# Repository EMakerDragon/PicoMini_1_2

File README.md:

RP2040とRP2350Aの小型開発ボードです。  
かなり適当な設計なので参考程度にしてください。  
JLCPCBの4層で製造しています。

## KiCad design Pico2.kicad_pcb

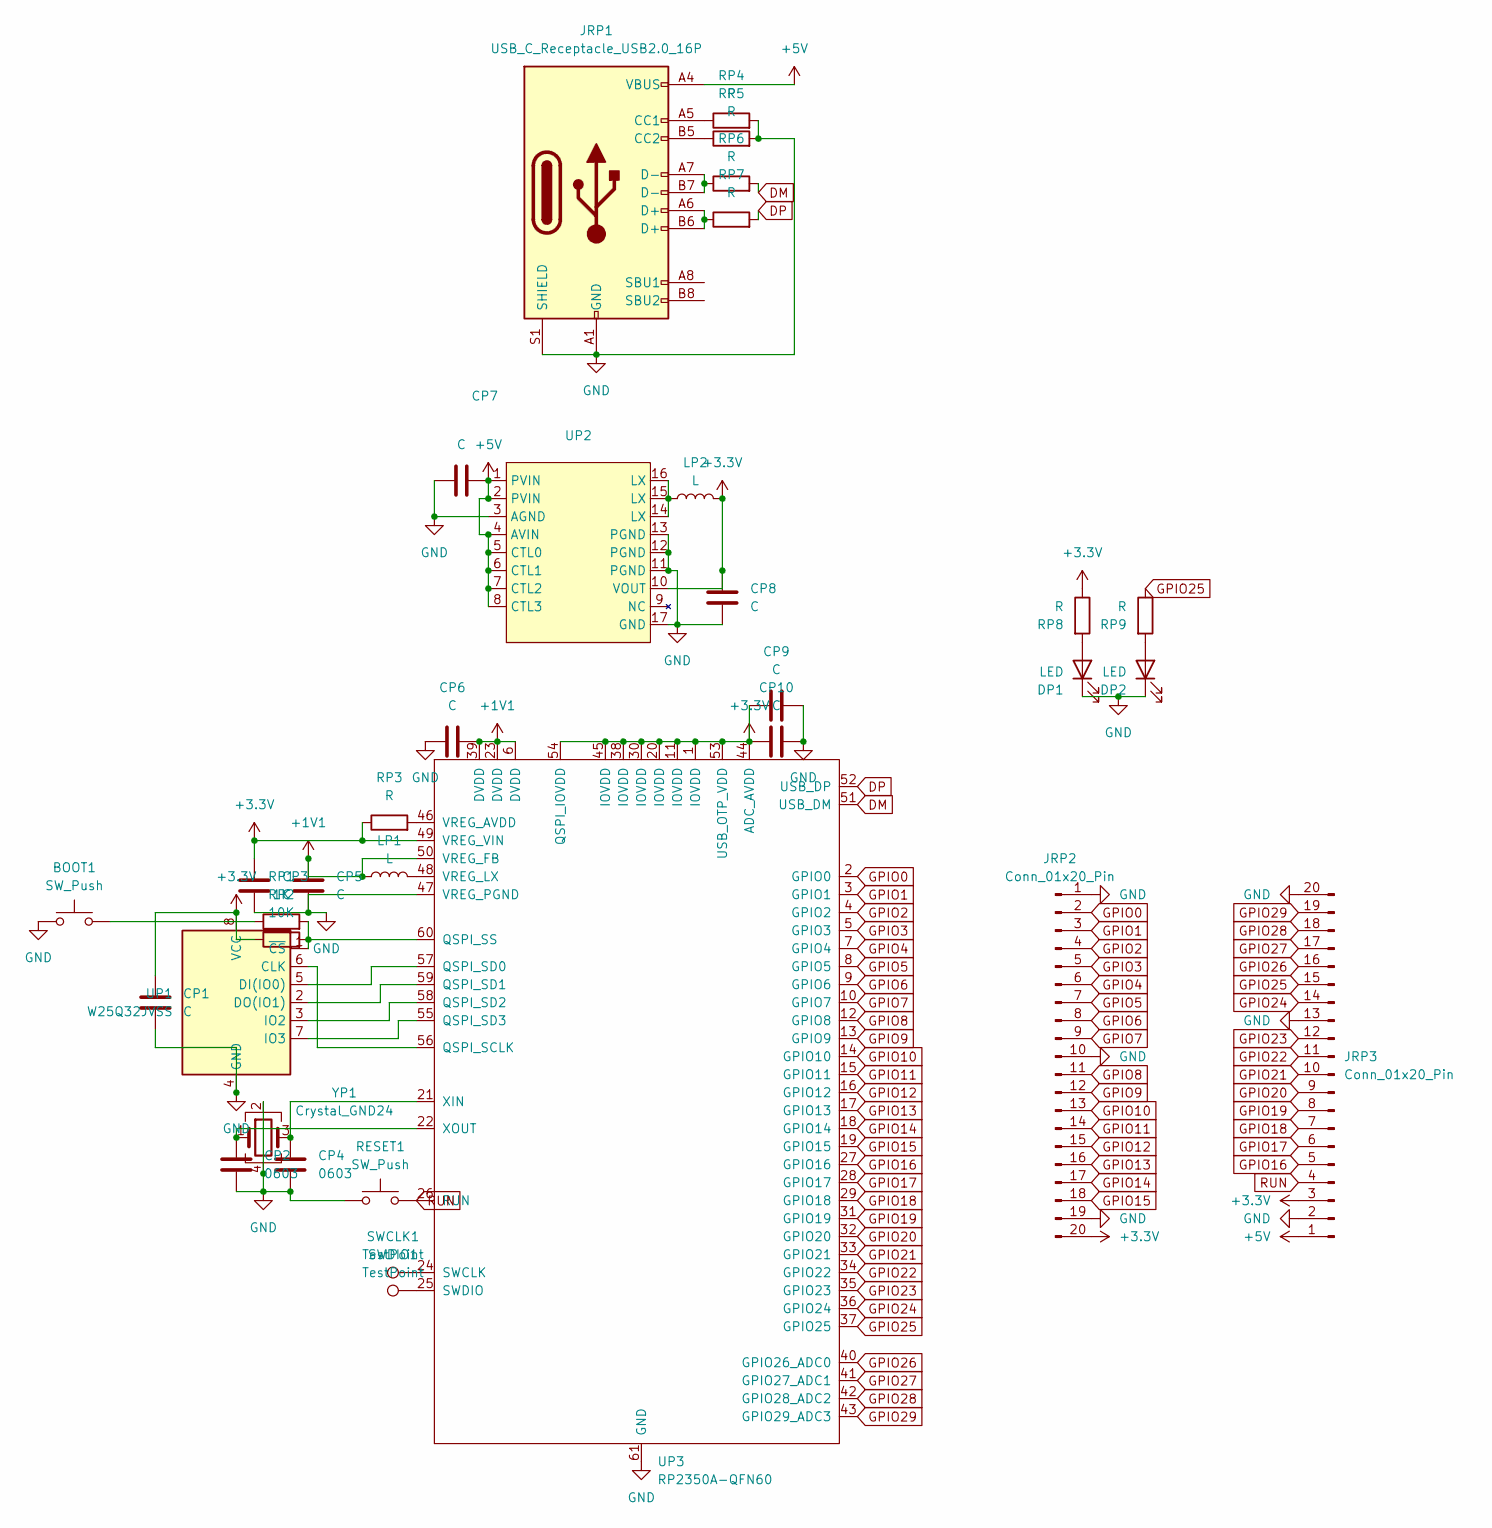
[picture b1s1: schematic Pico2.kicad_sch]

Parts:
BOOT1: SW_Push; SKRMAAE010
CP1, CP3, CP5, CP6, CP7, CP8, CP9, CP10: C; C_0805_2012Metric
CP2, CP4: 0603; C_0603_1608Metric
DP1, DP2: LED; LED_0805_2012Metric
JRP1: USB_C_Receptacle_USB2.0_16P; USB_C_Receptacle_G-Switch_GT-USB-7010ASV
JRP2, JRP3: Conn_01x20_Pin; PinHeader_1x20_P2.54mm_Vertical
LP1, LP2: L; L_1008_2520Metric
RESET1: SW_Push; SKRMAAE010
RP1: 1K; R_0603_1608Metric
RP2: 10K; R_0603_1608Metric
RP3, RP4, RP5, RP6, RP7, RP8, RP9: R; R_0603_1608Metric
SWCLK1: TestPoint; TestPoint_Pad_D1.0mm
SWDIO1: TestPoint; TestPoint_Pad_D1.0mm
UP1: W25Q32JVSS; U-PDFN-8
UP2: QFN-16-1EP_3x3mm_P0.5mm_EP1.7x1.7mm
UP3: RP2350A-QFN60; RP2350A_QFN-60_EP_7.75x7.75_Pitch0.4mm
YP1: Crystal_GND24; Crystal_SMD_SeikoEpson_TSX3225-4Pin_3.2x2.5mm

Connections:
+1V1: CP5.2, CP6.2, LP1.1, UP3.6 (DVDD), UP3.23 (DVDD), UP3.39 (DVDD), UP3.50 (VREG_FB)
+3.3V: CP1.2, CP3.2, CP8.1, CP9.1, CP10.1, JRP2.20, JRP3.3, LP2.2, RP2.1, RP3.1, RP8.1, UP1.8 (VCC), UP2.10 (VOUT), UP3.1 (IOVDD), UP3.11 (IOVDD), UP3.20 (IOVDD), UP3.30 (IOVDD), UP3.38 (IOVDD), UP3.44 (ADC_AVDD), UP3.45 (IOVDD), UP3.49 (VREG_VIN), UP3.53 (USB_OTP_VDD), UP3.54 (QSPI_IOVDD)
+5V: CP7.2, JRP1.A4 (VBUS), JRP1.A9 (VBUS), JRP1.B4 (VBUS), JRP1.B9 (VBUS), JRP3.1, UP2.1 (PVIN), UP2.2 (PVIN), UP2.4 (AVIN), UP2.5 (CTL0), UP2.6 (CTL1), UP2.7 (CTL2), UP2.8 (CTL3)
DM: RP6.2, UP3.51 (USB_DM)
DP: RP7.2, UP3.52 (USB_DP)
GND: BOOT1.1, CP1.1, CP2.2, CP3.1, CP4.2, CP5.1, CP6.1, CP7.1, CP8.2, CP9.2, CP10.2, DP1.1 (K), DP2.1 (K), JRP1.A1 (GND), JRP1.A12 (GND), JRP1.B1 (GND), JRP1.B12 (GND), JRP1.S1 (SHIELD), JRP2.1, JRP2.10, JRP2.19, JRP3.2, JRP3.13, JRP3.20, RESET1.1, RP4.2, RP5.2, UP1.4 (GND), UP2.3 (AGND), UP2.11 (PGND), UP2.12 (PGND), UP2.13 (PGND), UP2.17 (GND), UP3.47 (VREG_PGND), UP3.61 (GND), YP1.2, YP1.4
GPIO0: JRP2.2, UP3.2 (GPIO0)
GPIO1: JRP2.3, UP3.3 (GPIO1)
GPIO2: JRP2.4, UP3.4 (GPIO2)
GPIO3: JRP2.5, UP3.5 (GPIO3)
GPIO4: JRP2.6, UP3.7 (GPIO4)
GPIO5: JRP2.7, UP3.8 (GPIO5)
GPIO6: JRP2.8, UP3.9 (GPIO6)
GPIO7: JRP2.9, UP3.10 (GPIO7)
GPIO8: JRP2.11, UP3.12 (GPIO8)
GPIO9: JRP2.12, UP3.13 (GPIO9)
GPIO10: JRP2.13, UP3.14 (GPIO10)
GPIO11: JRP2.14, UP3.15 (GPIO11)
GPIO12: JRP2.15, UP3.16 (GPIO12)
GPIO13: JRP2.16, UP3.17 (GPIO13)
GPIO14: JRP2.17, UP3.18 (GPIO14)
GPIO15: JRP2.18, UP3.19 (GPIO15)
GPIO16: JRP3.5, UP3.27 (GPIO16)
GPIO17: JRP3.6, UP3.28 (GPIO17)
GPIO18: JRP3.7, UP3.29 (GPIO18)
GPIO19: JRP3.8, UP3.31 (GPIO19)
GPIO20: JRP3.9, UP3.32 (GPIO20)
GPIO21: JRP3.10, UP3.33 (GPIO21)
GPIO22: JRP3.11, UP3.34 (GPIO22)
GPIO23: JRP3.12, UP3.35 (GPIO23)
GPIO24: JRP3.14, UP3.36 (GPIO24)
GPIO25: JRP3.15, RP9.1, UP3.37 (GPIO25)
GPIO26: JRP3.16, UP3.40 (GPIO26_ADC0)
GPIO27: JRP3.17, UP3.41 (GPIO27_ADC1)
GPIO28: JRP3.18, UP3.42 (GPIO28_ADC2)
GPIO29: JRP3.19, UP3.43 (GPIO29_ADC3)
unnamed: BOOT1.2, RP1.1
unnamed: DP1.2 (A), RP8.2
unnamed: DP2.2 (A), RP9.2
unnamed: JRP1.A5 (CC1), RP4.1
unnamed: JRP1.B5 (CC2), RP5.1
unnamed: JRP1.A6 (D+), JRP1.B6 (D+), RP7.1
unnamed: JRP1.A7 (D-), JRP1.B7 (D-), RP6.1
unnamed: LP2.1, UP2.14 (LX), UP2.15 (LX), UP2.16 (LX)
unnamed: UP1.6 (CLK), UP3.56 (QSPI_SCLK)
unnamed: UP1.5 (DI(IO0)), UP3.57 (QSPI_SD0)
unnamed: UP1.2 (DO(IO1)), UP3.59 (QSPI_SD1)
unnamed: UP1.3 (IO2), UP3.58 (QSPI_SD2)
unnamed: UP1.7 (IO3), UP3.55 (QSPI_SD3)
unnamed: RP1.2, RP2.2, UP1.1 (~CS), UP3.60 (QSPI_SS)
unnamed: SWCLK1.1, UP3.24 (SWCLK)
unnamed: SWDIO1.1, UP3.25 (SWDIO)
unnamed: RP3.2, UP3.46 (VREG_AVDD)
unnamed: LP1.2, UP3.48 (VREG_LX)
unnamed: CP4.1, UP3.21 (XIN), YP1.3
unnamed: CP2.1, UP3.22 (XOUT), YP1.1
RUN: JRP3.4, RESET1.2, UP3.26 (RUN)

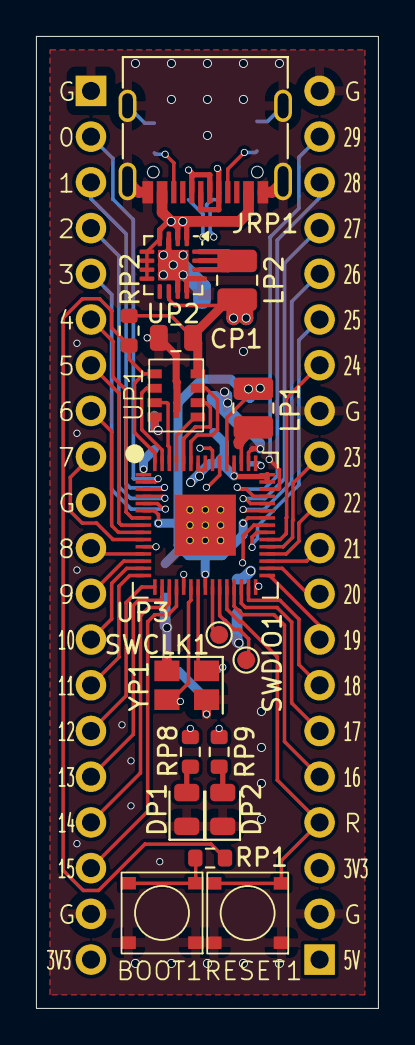
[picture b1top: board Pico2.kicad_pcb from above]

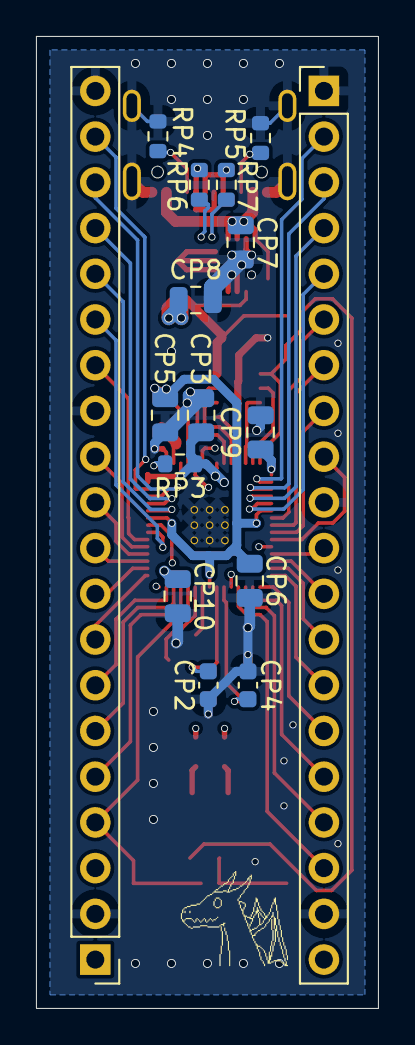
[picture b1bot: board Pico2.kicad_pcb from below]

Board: 4 copper layers, 19.0 x 54.0 mm, 34 parts (16 on the bottom side), 57 nets.

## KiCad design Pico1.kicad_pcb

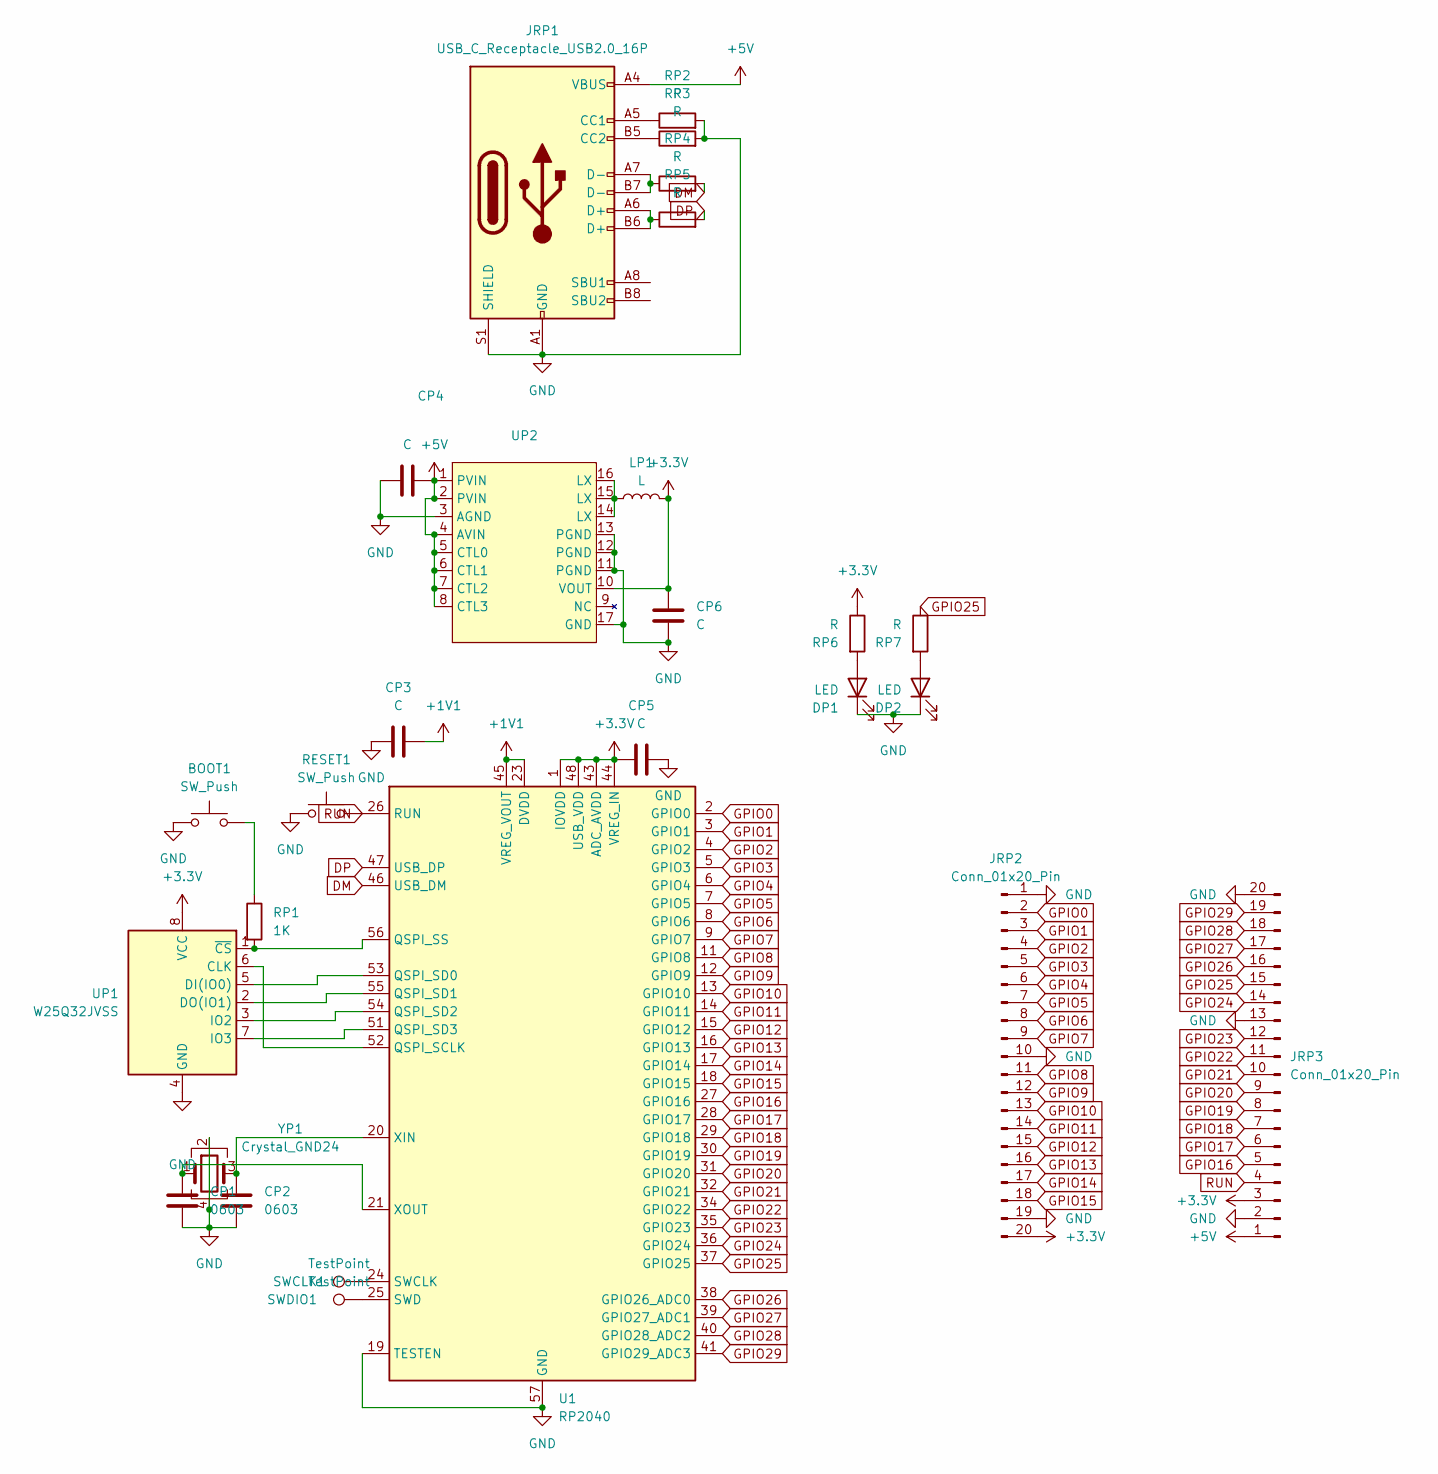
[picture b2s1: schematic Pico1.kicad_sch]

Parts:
BOOT1: SW_Push; SKRMAAE010
CP1, CP2: 0603; C_0603_1608Metric
CP3, CP4, CP5, CP6: C; C_0805_2012Metric
DP1, DP2: LED; LED_0805_2012Metric
JRP1: USB_C_Receptacle_USB2.0_16P; USB_C_Receptacle_G-Switch_GT-USB-7010ASV
JRP2, JRP3: Conn_01x20_Pin; PinHeader_1x20_P2.54mm_Vertical
LP1: L; L_1008_2520Metric
RESET1: SW_Push; SKRMAAE010
RP1: 1K; R_0603_1608Metric
RP2, RP3, RP4, RP5, RP6, RP7: R; R_0603_1608Metric
SWCLK1: TestPoint; TestPoint_Pad_D1.0mm
SWDIO1: TestPoint; TestPoint_Pad_D1.0mm
U1: RP2040; QFN-56-1EP_7x7mm_P0.4mm_EP3.2x3.2mm
UP1: W25Q32JVSS; U-PDFN-8
UP2: QFN-16-1EP_3x3mm_P0.5mm_EP1.7x1.7mm
YP1: Crystal_GND24; Crystal_SMD_SeikoEpson_TSX3225-4Pin_3.2x2.5mm

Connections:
+1V1: CP3.2, U1.23 (DVDD), U1.45 (VREG_VOUT), U1.50 (DVDD)
+3.3V: CP5.1, CP6.1, JRP2.20, JRP3.3, LP1.2, RP6.1, U1.1 (IOVDD), U1.10 (IOVDD), U1.22 (IOVDD), U1.33 (IOVDD), U1.42 (IOVDD), U1.43 (ADC_AVDD), U1.44 (VREG_IN), U1.48 (USB_VDD), U1.49 (IOVDD), UP1.8 (VCC), UP2.10 (VOUT)
+5V: CP4.2, JRP1.A4 (VBUS), JRP1.A9 (VBUS), JRP1.B4 (VBUS), JRP1.B9 (VBUS), JRP3.1, UP2.1 (PVIN), UP2.2 (PVIN), UP2.4 (AVIN), UP2.5 (CTL0), UP2.6 (CTL1), UP2.7 (CTL2), UP2.8 (CTL3)
DM: RP4.2, U1.46 (USB_DM)
DP: RP5.2, U1.47 (USB_DP)
GND: BOOT1.1, CP1.2, CP2.2, CP3.1, CP4.1, CP5.2, CP6.2, DP1.1 (K), DP2.1 (K), JRP1.A1 (GND), JRP1.A12 (GND), JRP1.B1 (GND), JRP1.B12 (GND), JRP1.S1 (SHIELD), JRP2.1, JRP2.10, JRP2.19, JRP3.2, JRP3.13, JRP3.20, RESET1.1, RP2.2, RP3.2, U1.19 (TESTEN), U1.57 (GND), UP1.4 (GND), UP2.3 (AGND), UP2.11 (PGND), UP2.12 (PGND), UP2.13 (PGND), UP2.17 (GND), YP1.2, YP1.4
GPIO0: JRP2.2, U1.2 (GPIO0)
GPIO1: JRP2.3, U1.3 (GPIO1)
GPIO2: JRP2.4, U1.4 (GPIO2)
GPIO3: JRP2.5, U1.5 (GPIO3)
GPIO4: JRP2.6, U1.6 (GPIO4)
GPIO5: JRP2.7, U1.7 (GPIO5)
GPIO6: JRP2.8, U1.8 (GPIO6)
GPIO7: JRP2.9, U1.9 (GPIO7)
GPIO8: JRP2.11, U1.11 (GPIO8)
GPIO9: JRP2.12, U1.12 (GPIO9)
GPIO10: JRP2.13, U1.13 (GPIO10)
GPIO11: JRP2.14, U1.14 (GPIO11)
GPIO12: JRP2.15, U1.15 (GPIO12)
GPIO13: JRP2.16, U1.16 (GPIO13)
GPIO14: JRP2.17, U1.17 (GPIO14)
GPIO15: JRP2.18, U1.18 (GPIO15)
GPIO16: JRP3.5, U1.27 (GPIO16)
GPIO17: JRP3.6, U1.28 (GPIO17)
GPIO18: JRP3.7, U1.29 (GPIO18)
GPIO19: JRP3.8, U1.30 (GPIO19)
GPIO20: JRP3.9, U1.31 (GPIO20)
GPIO21: JRP3.10, U1.32 (GPIO21)
GPIO22: JRP3.11, U1.34 (GPIO22)
GPIO23: JRP3.12, U1.35 (GPIO23)
GPIO24: JRP3.14, U1.36 (GPIO24)
GPIO25: JRP3.15, RP7.1, U1.37 (GPIO25)
GPIO26: JRP3.16, U1.38 (GPIO26_ADC0)
GPIO27: JRP3.17, U1.39 (GPIO27_ADC1)
GPIO28: JRP3.18, U1.40 (GPIO28_ADC2)
GPIO29: JRP3.19, U1.41 (GPIO29_ADC3)
unnamed: BOOT1.2, RP1.1
unnamed: DP1.2 (A), RP6.2
unnamed: DP2.2 (A), RP7.2
unnamed: JRP1.A5 (CC1), RP2.1
unnamed: JRP1.B5 (CC2), RP3.1
unnamed: JRP1.A6 (D+), JRP1.B6 (D+), RP5.1
unnamed: JRP1.A7 (D-), JRP1.B7 (D-), RP4.1
unnamed: LP1.1, UP2.14 (LX), UP2.15 (LX), UP2.16 (LX)
unnamed: U1.52 (QSPI_SCLK), UP1.6 (CLK)
unnamed: U1.53 (QSPI_SD0), UP1.5 (DI(IO0))
unnamed: U1.55 (QSPI_SD1), UP1.2 (DO(IO1))
unnamed: U1.54 (QSPI_SD2), UP1.3 (IO2)
unnamed: U1.51 (QSPI_SD3), UP1.7 (IO3)
unnamed: RP1.2, U1.56 (QSPI_SS), UP1.1 (~CS)
unnamed: SWCLK1.1, U1.24 (SWCLK)
unnamed: SWDIO1.1, U1.25 (SWD)
unnamed: CP2.1, U1.20 (XIN), YP1.3
unnamed: CP1.1, U1.21 (XOUT), YP1.1
RUN: JRP3.4, RESET1.2, U1.26 (RUN)

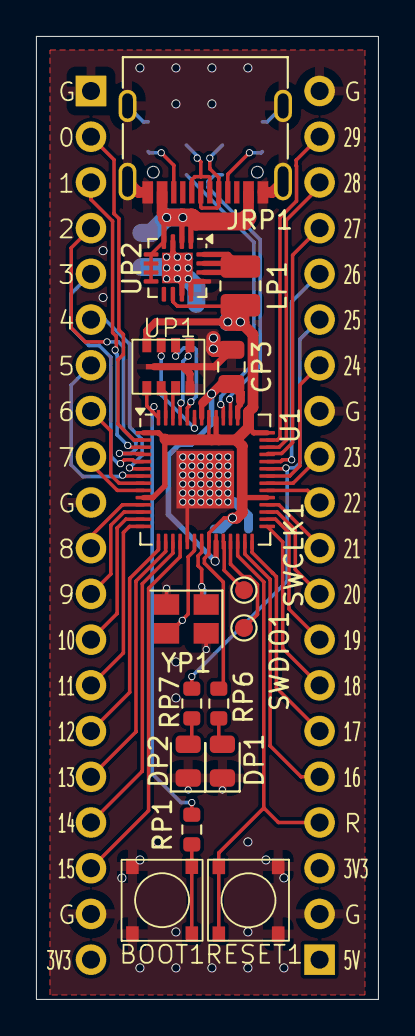
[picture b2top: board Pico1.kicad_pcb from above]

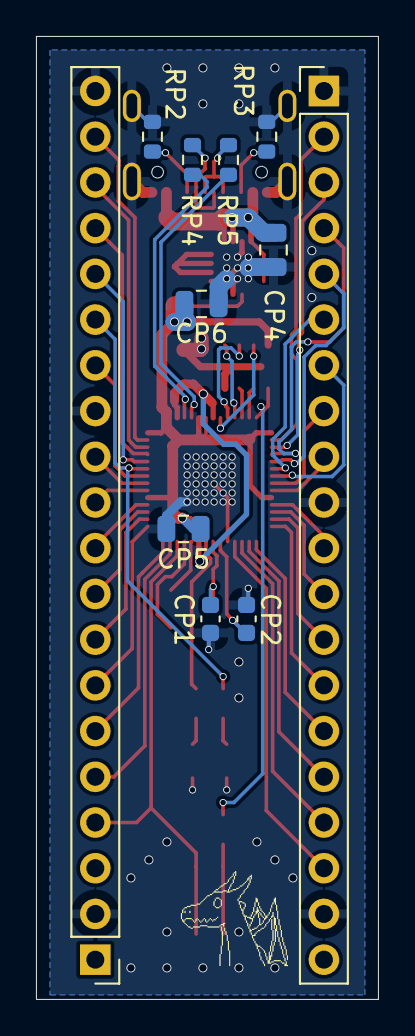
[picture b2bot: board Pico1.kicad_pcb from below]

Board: 4 copper layers, 19.0 x 53.5 mm, 27 parts (11 on the bottom side), 55 nets.
